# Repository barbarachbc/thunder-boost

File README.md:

# thunder-boost
Thunder Booster Pedal

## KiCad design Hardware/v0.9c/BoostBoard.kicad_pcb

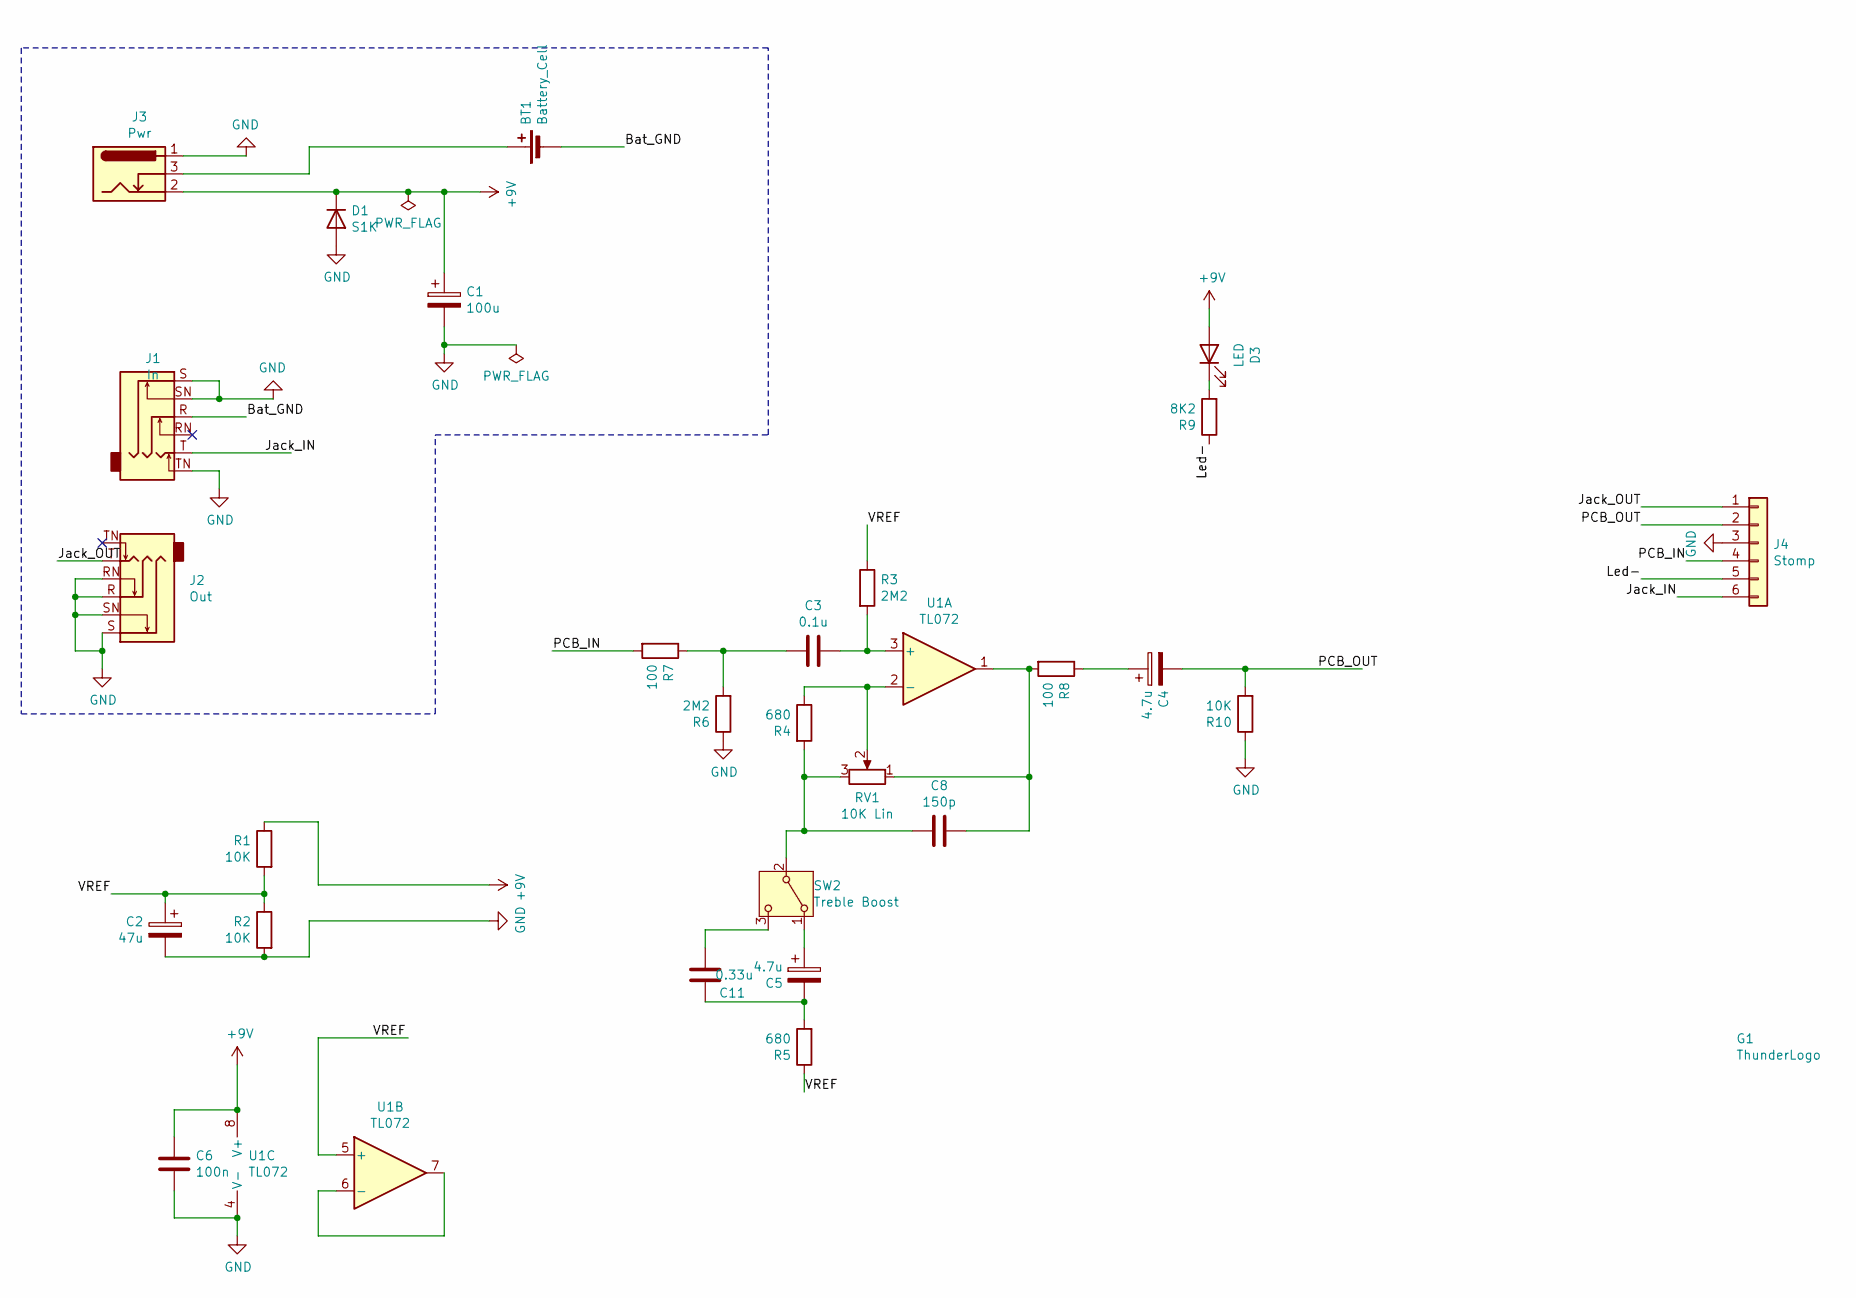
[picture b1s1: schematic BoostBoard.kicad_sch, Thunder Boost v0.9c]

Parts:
BT1: Battery_Cell; Conn_9V_Battery_Rotated; mpn 440005P
C1: 100u; CP_Elec_6.3x7.7; mpn 865080445010
C2: 47u; CP_Elec_6.3x5.4; mpn 865230243003
C3: 0.1u; C_1210_3225Metric; mpn CGA5L2C0G1H104J160AA
C4, C5: 4.7u; CP_Elec_4x5.4; mpn 865230440001
C6: 100n; C_0805_2012Metric; mpn 885012207016
C8: 150p; C_0805_2012Metric; mpn 885012007035
C11: 0.33u; C_0805_2012Metric; mpn C2012X7R1H334K125AA
D1: S1K; D_SMA; mpn S1K-13-F
D3: LED; LED_D3.0mm; mpn L-53LID
G1: ThunderLogo; ThunderImage
J1: In; Jack_6.35mm_Neutrik_NRJ6HM-1_Horizontal; mpn NRJ6HM-1-PRE
J2: Out; Jack_6.35mm_Neutrik_NRJ6HM-1_Horizontal; mpn NRJ6HM-1-PRE
J3: Pwr; DC_Barrel_Jack_Wurth_694106301002; mpn 694106301002
J4: Stomp; RibbonCableTerminal_1x06_P2.54mm_ForFootSwitch
R1, R2, R10: 10K; R_0805_2012Metric
R3, R6: 2M2; R_0805_2012Metric
R4, R5: 680; R_0805_2012Metric
R7, R8: 100; R_0805_2012Metric
R9: 8K2; R_0805_2012Metric
RV1: 10K Lin; Taiwan_Alpha_RV16AF-41; mpn RK09L1140A66
SW2: Treble Boost; CSS1210TB; mpn CSS1210TB
U1: TL072; TL072CDT-SO-8; mpn TL072CD

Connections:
+9V: C1.1, C6.1, D1.1 (K), D3.2 (A), J3.2, R1.1, U1.8 (V+)
/Bat_GND: BT1.2 (-), J1.R
/Jack_IN: J1.T, J4.6
/Jack_OUT: J2.T, J4.1
/Led-: J4.5, R9.1
/PCB_IN: J4.4, R7.2
/PCB_OUT: C4.2, J4.2, R10.2
/VREF: C2.1, R1.2, R2.1, R3.1, R5.1, U1.5 (+)
GND: C1.2, C2.2, C6.2, D1.2 (A), J1.S, J1.SN, J1.TN, J2.R, J2.RN, J2.S, J2.SN, J3.1, J4.3, R2.2, R6.1, R10.1, U1.4 (V-)
unnamed: BT1.1 (+), J3.3
unnamed: C3.1, R6.2, R7.1
unnamed: C3.2, R3.2, U1.3 (+)
unnamed: C4.1, R8.1
unnamed: C5.1, SW2.1 (A)
unnamed: C8.1, R4.2, RV1.3, SW2.2 (B)
unnamed: C8.2, R8.2, RV1.1, U1.1
unnamed: C11.1, SW2.3 (C)
unnamed: C5.2, C11.2, R5.2
unnamed: D3.1 (K), R9.2
unnamed: R4.1, RV1.2, U1.2 (-)
unnamed: U1.6 (-), U1.7

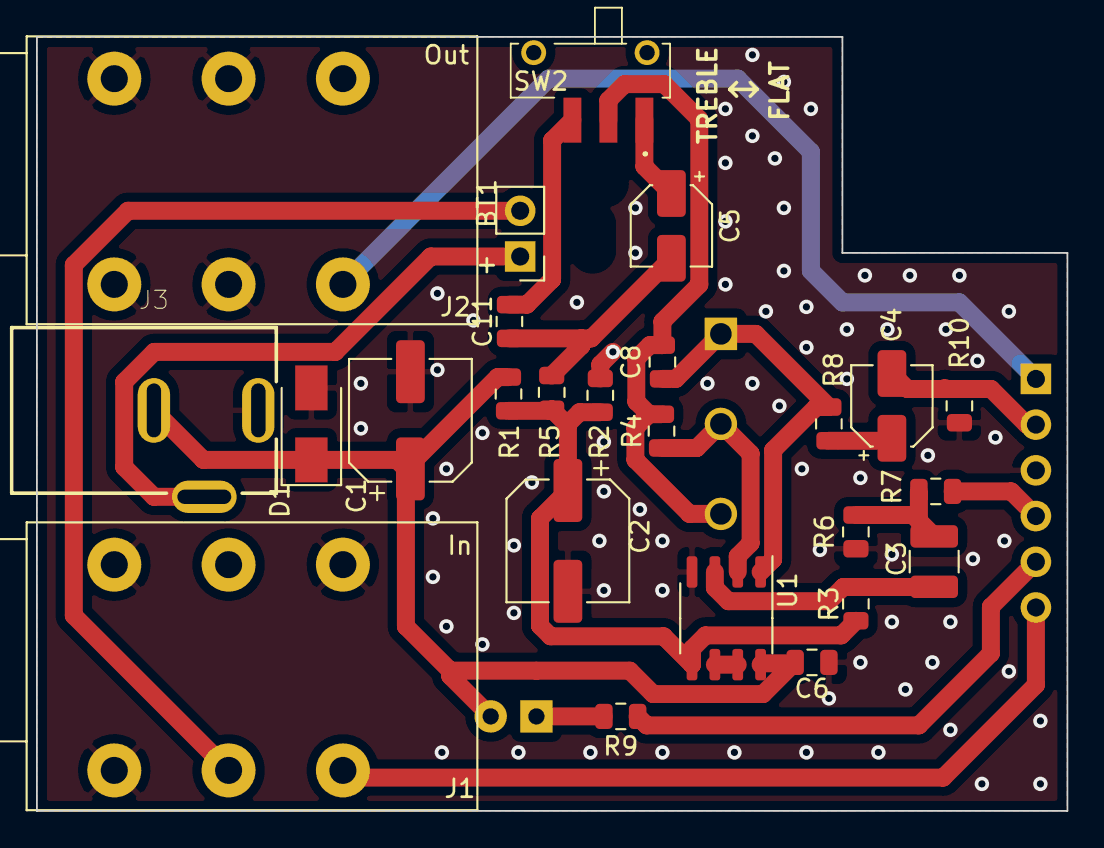
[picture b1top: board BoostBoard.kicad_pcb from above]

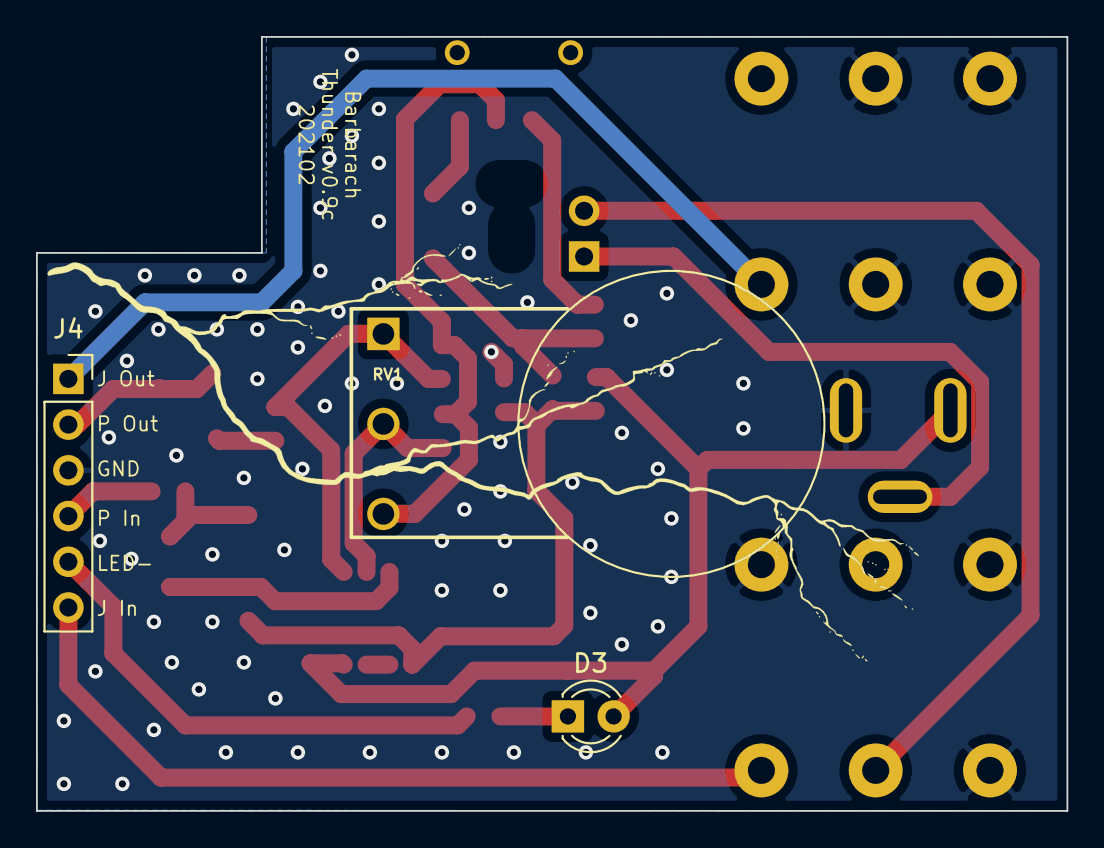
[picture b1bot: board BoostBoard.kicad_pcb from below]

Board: 2 copper layers, 57.2 x 43.0 mm, 29 parts (4 on the bottom side), 21 nets.
